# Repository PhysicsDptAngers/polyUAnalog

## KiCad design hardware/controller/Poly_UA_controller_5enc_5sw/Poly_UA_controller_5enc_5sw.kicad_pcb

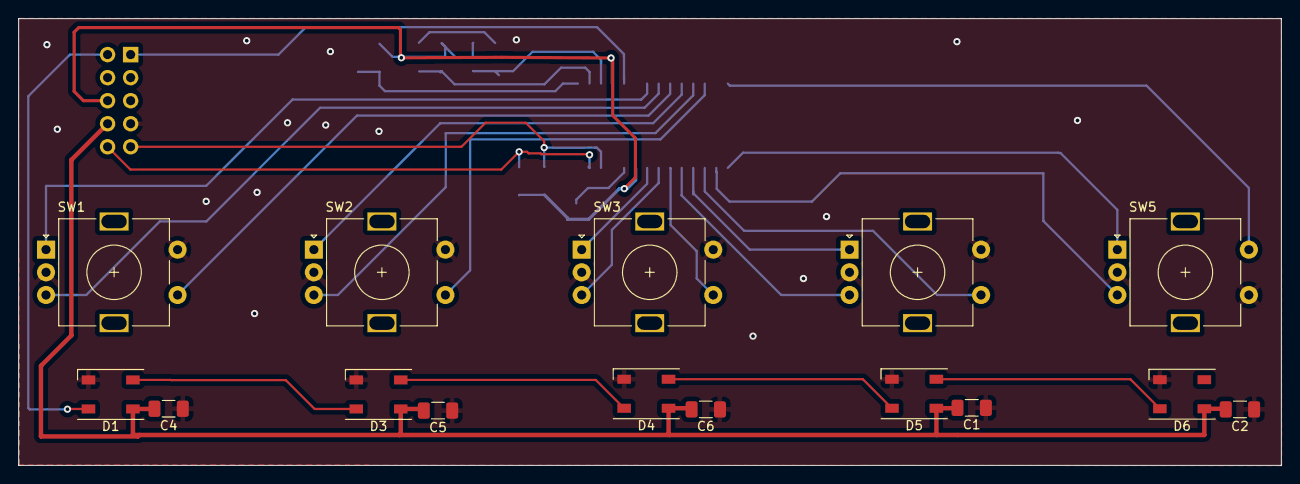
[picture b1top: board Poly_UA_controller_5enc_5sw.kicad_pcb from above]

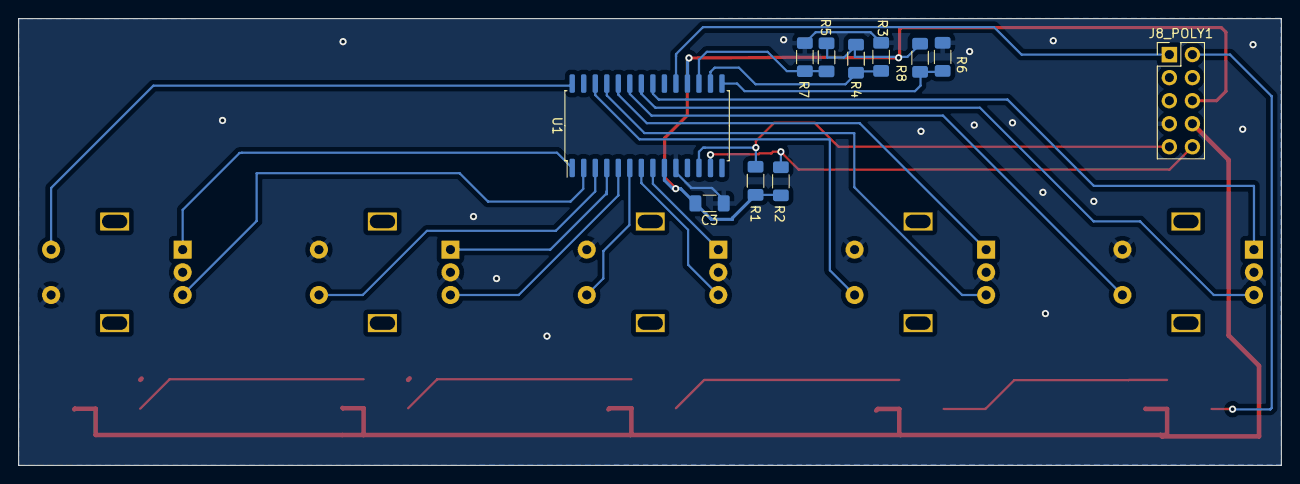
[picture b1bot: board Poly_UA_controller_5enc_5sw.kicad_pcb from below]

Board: 2 copper layers, 139.2 x 49.3 mm, 26 parts (11 on the bottom side), 29 nets.

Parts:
C1, C2, C4, C5, C6: 100n; C_1206_3216Metric_Pad1.33x1.80mm_HandSolder
C3: C; C_1206_3216Metric_Pad1.33x1.80mm_HandSolder
D1, D3, D4, D5, D6: SK6812; LED_SK6812_PLCC4_5.0x5.0mm_P3.2mm
J8_POLY1: Conn_Env; PinHeader_2x05_P2.54mm_Vertical
R1, R2: 4K7; R_1206_3216Metric_Pad1.30x1.75mm_HandSolder
R3, R4, R5, R6, R7, R8: 0; R_1206_3216Metric_Pad1.30x1.75mm_HandSolder
SW1, SW2, SW3, SW4, SW5: RotaryEncoder_Switch; RotaryEncoder_Alps_EC11E-Switch_Vertical_H20mm
U1: MCP23017_SO; SOIC-28W_7.5x17.9mm_P1.27mm

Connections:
GND: C1.1, C2.1, C3.1, C4.1, C5.1, C6.1, D1.1 (VSS), D3.1 (VSS), D4.1 (VSS), D5.1 (VSS), D6.1 (VSS), J8_POLY1.7, R4.2, R7.2, R8.2, SW1.C, SW1.S2, SW2.C, SW2.S2, SW3.C, SW3.S2, SW4.C, SW4.S2, SW5.C, SW5.S1, U1.10 (VSS)
LED_DATA_IN: D1.2 (DIN), J8_POLY1.2
LED_POWER: C1.2, C2.2, C4.2, C5.2, C6.2, D1.3 (VDD), D3.3 (VDD), D4.3 (VDD), D5.3 (VDD), D6.3 (VDD), J8_POLY1.8
MCP23017_IRQ: J8_POLY1.1, U1.19 (INTB)
unnamed: D1.4 (DOUT), D3.2 (DIN)
unnamed: D3.4 (DOUT), D4.2 (DIN)
unnamed: D4.4 (DOUT), D5.2 (DIN)
unnamed: D5.4 (DOUT), D6.2 (DIN)
unnamed: R6.2, R8.1, U1.15 (A0)
unnamed: R3.2, R4.1, U1.16 (A1)
unnamed: R5.2, R7.1, U1.17 (A2)
R1_A: SW1.A, U1.21 (GPA0)
R1_B: SW1.B, U1.22 (GPA1)
R2_A: SW2.A, U1.24 (GPA3)
R2_B: SW2.B, U1.25 (GPA4)
R3_A: SW3.A, U1.8 (GPB7)
R3_B: SW3.B, U1.7 (GPB6)
R4_A: SW4.A, U1.4 (GPB3)
R4_B: SW4.B, U1.5 (GPB4)
R5_A: SW5.A, U1.1 (GPB0)
R5_B: SW5.B, U1.2 (GPB1)
SCK: J8_POLY1.9, R2.1, U1.12 (SCK)
SDA: J8_POLY1.10, R1.2, U1.13 (SDA)
SW_1: SW1.S1, U1.23 (GPA2)
SW_2: SW2.S1, U1.26 (GPA5)
SW_3: SW3.S1, U1.6 (GPB5)
SW_4: SW4.S1, U1.3 (GPB2)
SW_5: SW5.S2, U1.28 (GPA7)
VCC: C3.2, J8_POLY1.6, R1.1, R2.2, R3.1, R5.1, R6.1, U1.9 (VDD), U1.18 (~RESET)

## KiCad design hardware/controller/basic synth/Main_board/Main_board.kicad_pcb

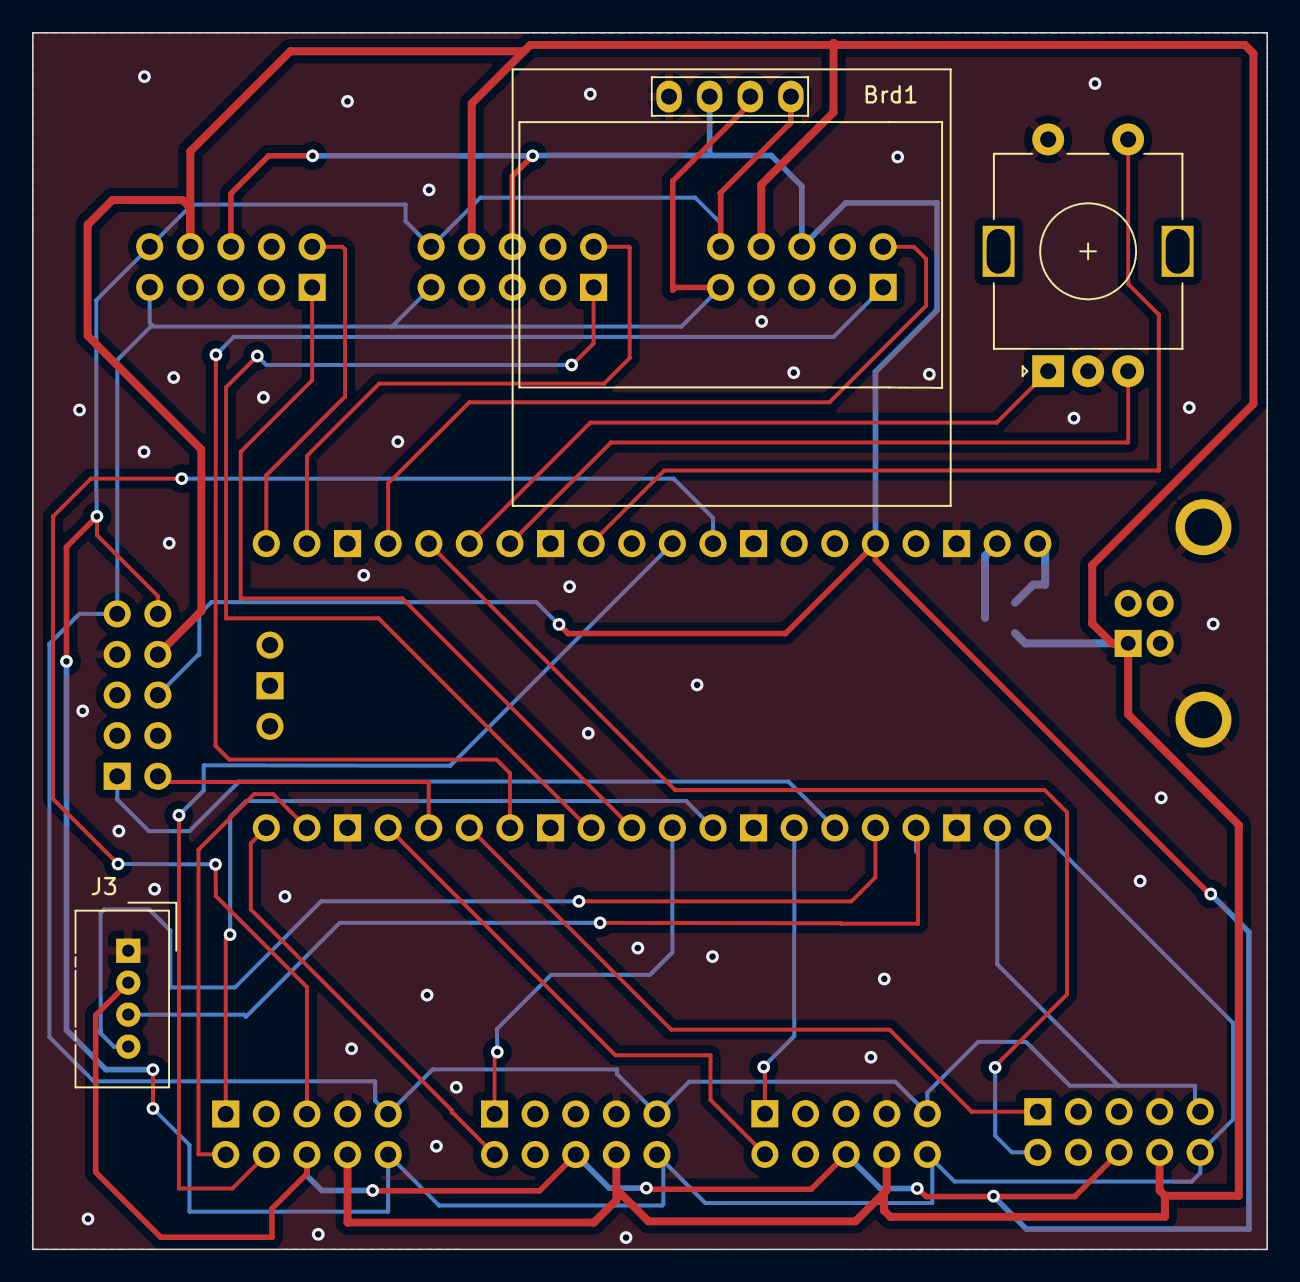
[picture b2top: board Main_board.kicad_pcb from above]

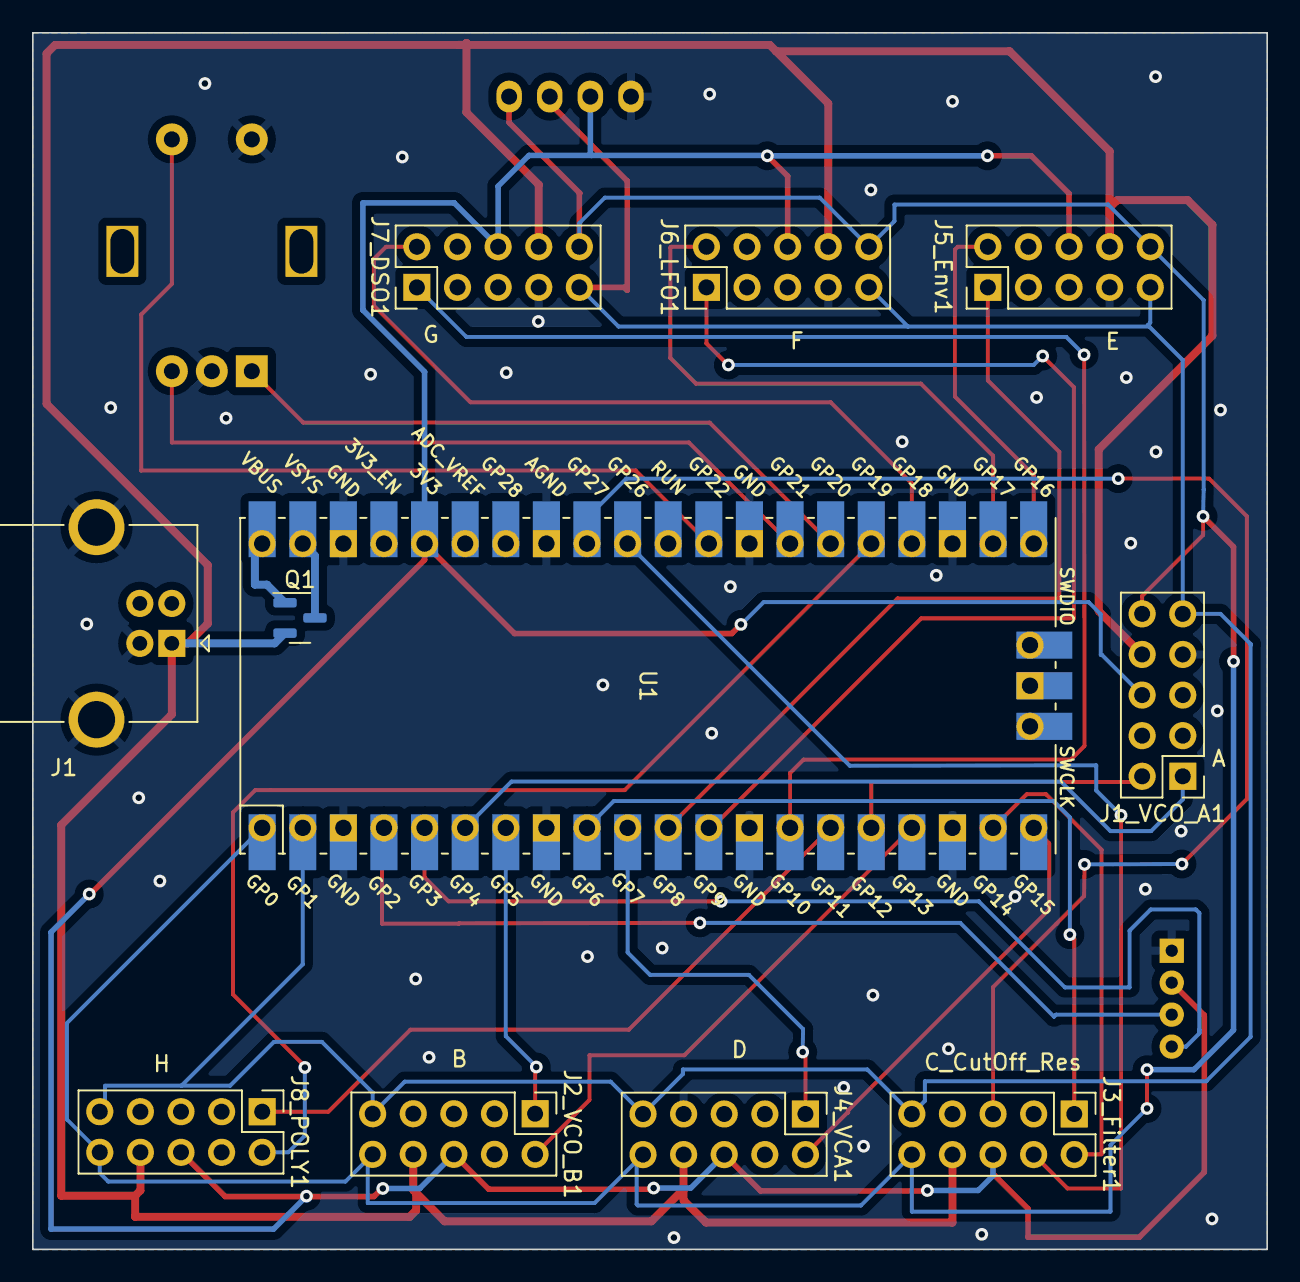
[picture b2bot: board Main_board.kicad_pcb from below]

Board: 2 copper layers, 77.2 x 76.1 mm, 14 parts (11 on the bottom side), 30 nets.

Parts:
Brd1: SSD1306; 128x64OLED
J1: USB_B; USB_B_OST_USB-B1HSxx_Horizontal
J1_VCO_A1: Conn_VCO_A; PinHeader_2x05_P2.54mm_Vertical
J2_VCO_B1: Conn_VCO_B; PinHeader_2x05_P2.54mm_Vertical
J3: Conn_01x04_Socket; NS-Tech_Grove_1x04_P2mm_Vertical
J3_Filter1: Conn_Filter; PinHeader_2x05_P2.54mm_Vertical
J4_VCA1: Conn_VCA; PinHeader_2x05_P2.54mm_Vertical
J5_Env1, J6_LFO1, J7_DSO1, J8_POLY1: Conn_Env; PinHeader_2x05_P2.54mm_Vertical
Q1: BS170F; SOT-23
SW2: RotaryEncoder_Switch; RotaryEncoder_Alps_EC11E-Switch_Vertical_H20mm
U1: Pico; RPi_Pico_SMD_TH

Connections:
3V3: Brd1.2 (VCC), J1_VCO_A1.6, J2_VCO_B1.6, J3.2, J3_Filter1.6, J4_VCA1.6, J5_Env1.6, J6_LFO1.6, J7_DSO1.6, J8_POLY1.6, U1.36 (3V3)
ADC_CUTOFF: J3_Filter1.4, U1.31 (GPIO26_ADC0)
ADC_Resonance: J3_Filter1.5, U1.32 (GPIO27_ADC1)
ENC_PRESET_A: SW2.A, U1.26 (GPIO20)
ENC_PRESET_B: SW2.B, U1.27 (GPIO21)
GND: Brd1.1 (GND), J1.4 (GND), J1.5 (Shield), J1_VCO_A1.7, J2_VCO_B1.7, J3.1, J3_Filter1.7, J4_VCA1.7, J5_Env1.7, J6_LFO1.7, J7_DSO1.7, J8_POLY1.7, SW2.C, SW2.S2, U1.3 (GND), U1.8 (GND), U1.13 (GND), U1.18 (GND), U1.23 (GND), U1.28 (GND), U1.33 (AGND), U1.38 (GND)
IC0_SCL: Brd1.3 (SCL), J1_VCO_A1.9, J2_VCO_B1.9, J3_Filter1.9, J4_VCA1.9, J5_Env1.9, J6_LFO1.9, J7_DSO1.9, J8_POLY1.9, U1.2 (GPIO1)
IC0_SDA: Brd1.4 (SDA), J1_VCO_A1.10, J2_VCO_B1.10, J3_Filter1.10, J4_VCA1.10, J5_Env1.10, J6_LFO1.10, J7_DSO1.10, J8_POLY1.10, U1.1 (GPIO0)
IC1_SCL: J3.4, U1.5 (GPIO3)
IC1_SDA: J3.3, U1.4 (GPIO2)
INT_A: J1_VCO_A1.1, U1.6 (GPIO4)
INT_B: J2_VCO_B1.1, U1.7 (GPIO5)
INT_C: J3_Filter1.1, U1.9 (GPIO6)
INT_D: J4_VCA1.1, U1.10 (GPIO7)
INT_E: J5_Env1.1, U1.11 (GPIO8)
INT_F: J6_LFO1.1, U1.12 (GPIO9)
INT_G: J7_DSO1.1, U1.14 (GPIO10)
INT_H: J8_POLY1.1, U1.15 (GPIO11)
LED_A: J1_VCO_A1.2, U1.16 (GPIO12)
LED_B: J2_VCO_B1.2, U1.17 (GPIO13)
LED_C: J3_Filter1.2, U1.19 (GPIO14)
LED_D: J4_VCA1.2, U1.20 (GPIO15)
LED_E: J5_Env1.2, U1.21 (GPIO16)
LED_F: J6_LFO1.2, U1.22 (GPIO17)
LED_G: J7_DSO1.2, U1.24 (GPIO18)
LED_H: J8_POLY1.2, U1.25 (GPIO19)
LED_POWER: J1.1 (VBUS), J1_VCO_A1.8, J2_VCO_B1.8, J3_Filter1.8, J4_VCA1.8, J5_Env1.8, J6_LFO1.8, J7_DSO1.8, J8_POLY1.8, Q1.2 (S)
unnamed: Q1.1 (G), U1.40 (VBUS)
SWITCH_ENCODER: SW2.S1, U1.29 (GPIO22)
VBUS: Q1.3 (D), U1.39 (VSYS)
